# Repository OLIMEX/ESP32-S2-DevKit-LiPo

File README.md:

# ESP32-S2-DevKit-LiPo
ESP32-S2 IoT developement board with WiFi, USB programmer, RGB LED, LiPo charger, GPIOs

Product page: https://www.olimex.com/Products/IoT/ESP32/ESP32-DevKit-LiPo/open-source-hardware

## License
* Hardware is released under CERN Open Hardware Licence Version 2 -
Strongly Reciprocal
* Software is released under GPL3 Licensee
* Documentation is released under CC BY-SA 3.0

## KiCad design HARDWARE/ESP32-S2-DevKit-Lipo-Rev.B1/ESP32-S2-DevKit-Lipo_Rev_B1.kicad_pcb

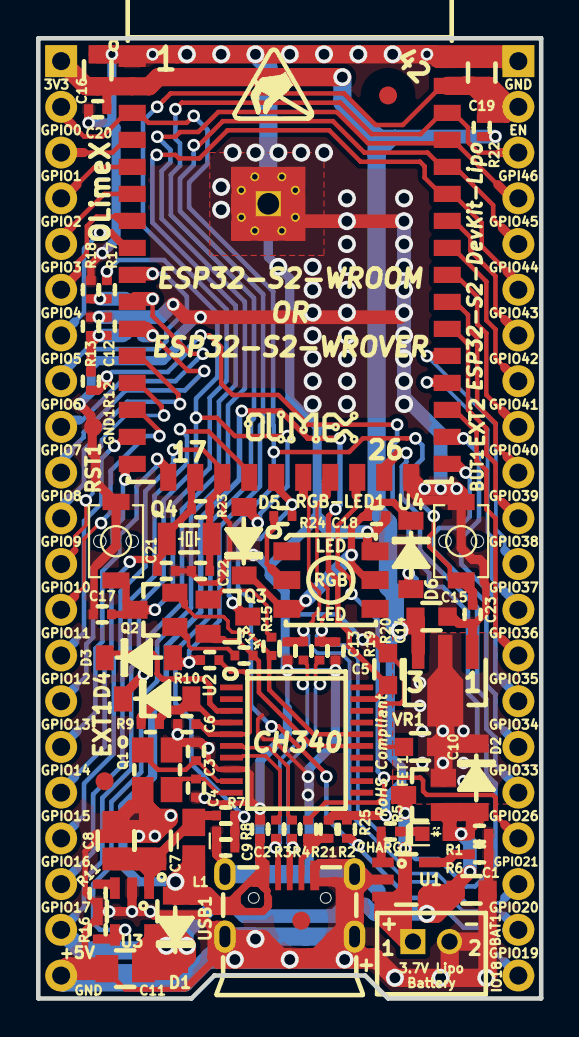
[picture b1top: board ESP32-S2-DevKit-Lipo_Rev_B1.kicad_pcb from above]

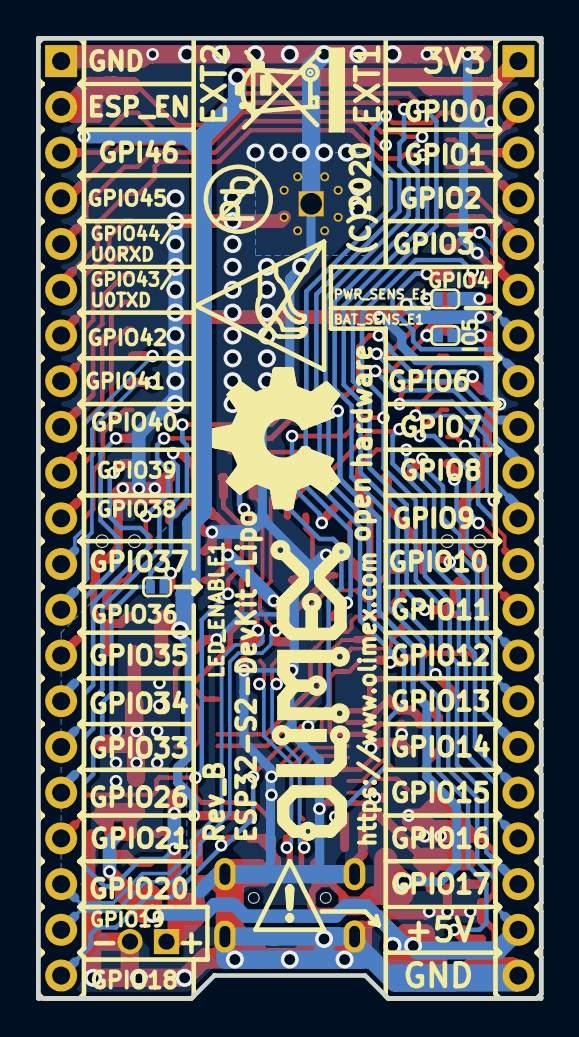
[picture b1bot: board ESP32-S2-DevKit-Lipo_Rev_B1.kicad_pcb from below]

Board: 2 copper layers, 27.9 x 53.3 mm, 87 parts (10 on the bottom side), 68 nets.

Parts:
BAT1: DW02S; LIPO_BAT_VERTICAL_DW02S
BAT_SENS_E1: Opened; SJ_1_SMALLER
BUT1: IT-1185AU2-160G-G-TR; IT1185AU2_V2
C1, C5: 10uF/6.3V/20%/X5R/C0603; C_0603_5MIL_DWS
C2, C17, C23: NA(100nF/10V/10%/X7R/C0402); C_0402_5MIL_DWS
C3, C4: 27pF/50V/5%/C0G/C0402; C_0402_5MIL_DWS
C6, C12, C18, C20: 100nF/10V/10%/X7R/C0402; C_0402_5MIL_DWS
C7, C8, C11: NA(47uF/6.3V/20%/X5R/C0805); C_0805_5MIL_DWS
C9: NA(C0402); C_0402_5MIL_DWS
C10, C15, C16: 22uF/6.3V/20%/X5R/C0603; C_0603_5MIL_DWS
C13, C14, C21, C22: NA(22pF/50V/5%/COG/C0402); C_0402_5MIL_DWS
C19: 1uF/10V/10%/X5R/C0603; C_0603_5MIL_DWS
CHARG1: LED/YELLOW/0603; LED_0603_KA
D1, D2, D3, D4, D6: 1N5819S4/SOD123; SOD-123_1C-2A_KA
D5: 1N4148W/SOD123; SOD-123_1C-2A_KA
EXT1, EXT2: HN1x21
FET1: WPM2015-3/TR; SOT23
FID1, FID2, FID3: Fiducial; Fiducial1x3
GND1: TESTPAD; TESTPAD_40-ROUND
L1: NA(FB0805/600R/2A); L_0805_5MIL_DWS
LED_ENABLE1: Soldered; SJ_1_SMALLER
Logo_OSHW: LOGO_OPENHARDWARE_8x8
Olimex_Logo_Big: OLIMEX_LOGO_TB
Olimex_Logo_Small: LOGO_OLIMEX_80
PWR_SENS_E1: Opened; SJ_1_SMALLER
Q1: Q12MHz/20pF/10ppm/4P/3.2x2.5mm; TSX-3.2x2.5mm_GND(3)
Q2, Q3: BC817-40(SOT23); SOT23
Q4: NA(Q32.768kHz/12.5pF/2P/SMD1206); CM7V-T1A(Crystal_Package-1206_3.20x1.50x0.65mm)
R1, R9, R10, R17, R22: 10k/R0402; R_0402_5MIL_DWS
R2, R16: NA(10k/R0402); R_0402_5MIL_DWS
R3, R4, R24: 22R/R0402; R_0402_5MIL_DWS
R5, R6, R14, R15: 2.2k/R0402; R_0402_5MIL_DWS
R7: NA(1.1k/R0402); R_0402_5MIL_DWS
R8: NA(2.2k/R0402); R_0402_5MIL_DWS
R11: NA(13k/1%/R0402); R_0402_5MIL_DWS
R12: 4.7M/R0402; R_0402_5MIL_DWS
R13, R25: 470k/R0402; R_0402_5MIL_DWS
R18: 1k/R0402; R_0402_5MIL_DWS
R19, R20, R21: NA(22R/R0402); R_0402_5MIL_DWS
R23: NA(10M/R0402); R_0402_5MIL_DWS
RGB-LED1: WS2812S(5X5MM); WS2812S(5x5MM)
RST1: IT-1185AU2-160G-G-TR; IT1185AU2_V2
Sign-Antistatic: LOGO_ANTISTATIC_1
Sign-Pb-Free: LOGO_PBFREE
Sign_Antistatic: Val**; LOGO_ANTISTATIC_SMALL_4.5mmX2.8mm
Sign_RecycleBin: LOGO_RECYCLEBIN_1
U1: BL4054B-42TPRN(SOT23-5); SOT-23-5
U2: CH340T(SSOP20W); SSOP-20W
U3: NA(SY6280AAC(SOT23-5)); SOT-23-5
U4: ESP32-S2-WROVER_and_WROOM(PCB,-I(IPEX))-Universal; ESP32-S2-WROVER_MODULE
USB1: MISB-SWMM-5B-LF(USB_MICRO); USB-MICRO_MISB-SWMM-5B_LF
VR1: MCP1700T-3302E/MB(SOT89-3); SOT89-3

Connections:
+3V3: C15.1, C16.1, C20.2, EXT1.1, R2.1, R22.1, R25.1, U4.2, VR1.3
+5V: C1.1, C11.1, CHARG1.2, D1.1, D2.2, D5.2, EXT1.20, FET1.1, R1.1, R17.1, U1.4, U3.5
/+5V_USB: C2.2, C5.1, D1.2, L1.1, R9.1, U2.19, USB1.1
/ESP_EN\CHIP_PU: C17.2, C19.1, EXT2.2, Q2.3, R22.2, RST1.1, U4.41
/GPI46\USB-VBUS_DET: C9.2, EXT2.3, R7.1, R8.2, U4.40
/GPIO0\BUT: BUT1.1, C23.2, EXT1.2, Q3.3, U4.3
/GPIO1: EXT1.3, U4.4
/GPIO2: EXT1.4, U4.5
/GPIO3: EXT1.5, U4.6
/GPIO4: EXT1.6, U4.7
/GPIO5: EXT1.7, U4.8
/GPIO6: EXT1.8, U4.9
/GPIO7\PWR_SENS: EXT1.9, PWR_SENS_E1.2, U4.10
/GPIO8\BAT_SENS: BAT_SENS_E1.2, EXT1.10, U4.11
/GPIO9: EXT1.11, U4.12
/GPIO10: EXT1.12, U4.13
/GPIO11: EXT1.13, U4.14
/GPIO12: EXT1.14, U4.15
/GPIO13: EXT1.15, U4.16
/GPIO14: EXT1.16, U4.17
/GPIO15\XTAL_32K_P: C21.2, EXT1.17, Q4.1, R23.2, U4.18
/GPIO16\XTAL_32K_N: C22.2, EXT1.18, Q4.2, R23.1, U4.19
/GPIO17: EXT1.19, U4.20
/GPIO18\RGB_LED: EXT2.21, R24.1, R25.2, U4.21
/GPIO19\USB_D-: C13.1, EXT2.20, R19.2, U4.22
/GPIO20\USB_D+: C14.1, EXT2.19, R20.2, U4.23
/GPIO21\USB-ID: EXT2.18, R21.2, U4.24
/GPIO26: EXT2.17, U4.25
/GPIO33: EXT2.16, U4.27
/GPIO34: EXT2.15, U4.28
/GPIO35: EXT2.14, U4.29
/GPIO36: EXT2.13, U4.30
/GPIO37: EXT2.12, U4.31
/GPIO38: EXT2.11, U4.32
/GPIO39: EXT2.10, U4.33
/GPIO40: EXT2.9, U4.34
/GPIO41: EXT2.8, U4.35
/GPIO42: EXT2.7, U4.36
/GPIO43\U0TXD: D4.1, EXT2.6, U4.37
/GPIO44\U0RXD: D3.2, EXT2.5, R10.2, U4.38
/GPIO45\USB-DRV: EXT2.4, R16.2, U3.4, U4.39
/UD+: R4.2, U2.6
/UD-: R3.2, U2.7
/USB-ID: R2.2, R21.1, USB1.4
/USB_D+: R4.1, R20.1, USB1.3
/USB_D-: R3.1, R19.1, USB1.2
/Vin: C10.1, D2.1, FET1.2, VR1.2
GND: BAT1.2, BUT1.2, C1.2, C2.1, C3.2, C4.2, C5.2, C6.2, C7.1, C8.1, C9.1, C10.2, C11.2, C12.1, C13.2, C14.2, C15.2, C16.2, C17.1, C18.1, C19.2, C20.1, C21.1, C22.1, C23.1, EXT1.21, EXT2.1, GND1.1, Q1.3, R1.2, R6.2, R8.1, R11.1, R13.2, R16.1, R18.2, RGB-LED1.6, RST1.2, U1.2, U2.8, U3.2, U4.1, U4.26, U4.42, U4.43, USB1.0, USB1.5, VR1.1
unnamed: BAT_SENS_E1.1, C12.2, R12.2, R13.1
unnamed: C3.1, Q1.1, U2.9
unnamed: C4.1, Q1.2, U2.10
unnamed: C6.1, R10.1, U2.5
unnamed: C7.2, C8.2, L1.2, R7.2, U3.1
unnamed: C18.2, D5.1, D6.1, RGB-LED1.3, RGB-LED1.5
unnamed: CHARG1.1, R5.1
unnamed: D3.1, U2.3
unnamed: D4.2, R9.2, U2.4
unnamed: D6.2, LED_ENABLE1.1
unnamed: PWR_SENS_E1.1, R17.2, R18.1
unnamed: Q2.1, R14.2
unnamed: Q2.2, R15.1, U2.16
unnamed: Q3.1, R15.2
unnamed: Q3.2, R14.1, U2.15
unnamed: R5.2, U1.1
unnamed: R6.1, U1.5
unnamed: R11.2, U3.3
unnamed: R24.2, RGB-LED1.2
VBAT: BAT1.1, FET1.3, LED_ENABLE1.2, R12.1, U1.3

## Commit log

2020-10-27 initial upload CAD files
2020-10-29 Product page link fixed
2026-03-12 new demo
    added arduino demos
2026-04-07 Update
    Added manual
2026-04-08 Update
    Added esphome and platformio configuration files
2026-04-09 Update
    Changed pictures to fit the product

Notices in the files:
HARDWARE/ESP32-S2-DevKit-Lipo-Rev.B1/ESP32-S2-DevKit-Lipo_Rev_B1.kicad_pcb:
(C)2020
